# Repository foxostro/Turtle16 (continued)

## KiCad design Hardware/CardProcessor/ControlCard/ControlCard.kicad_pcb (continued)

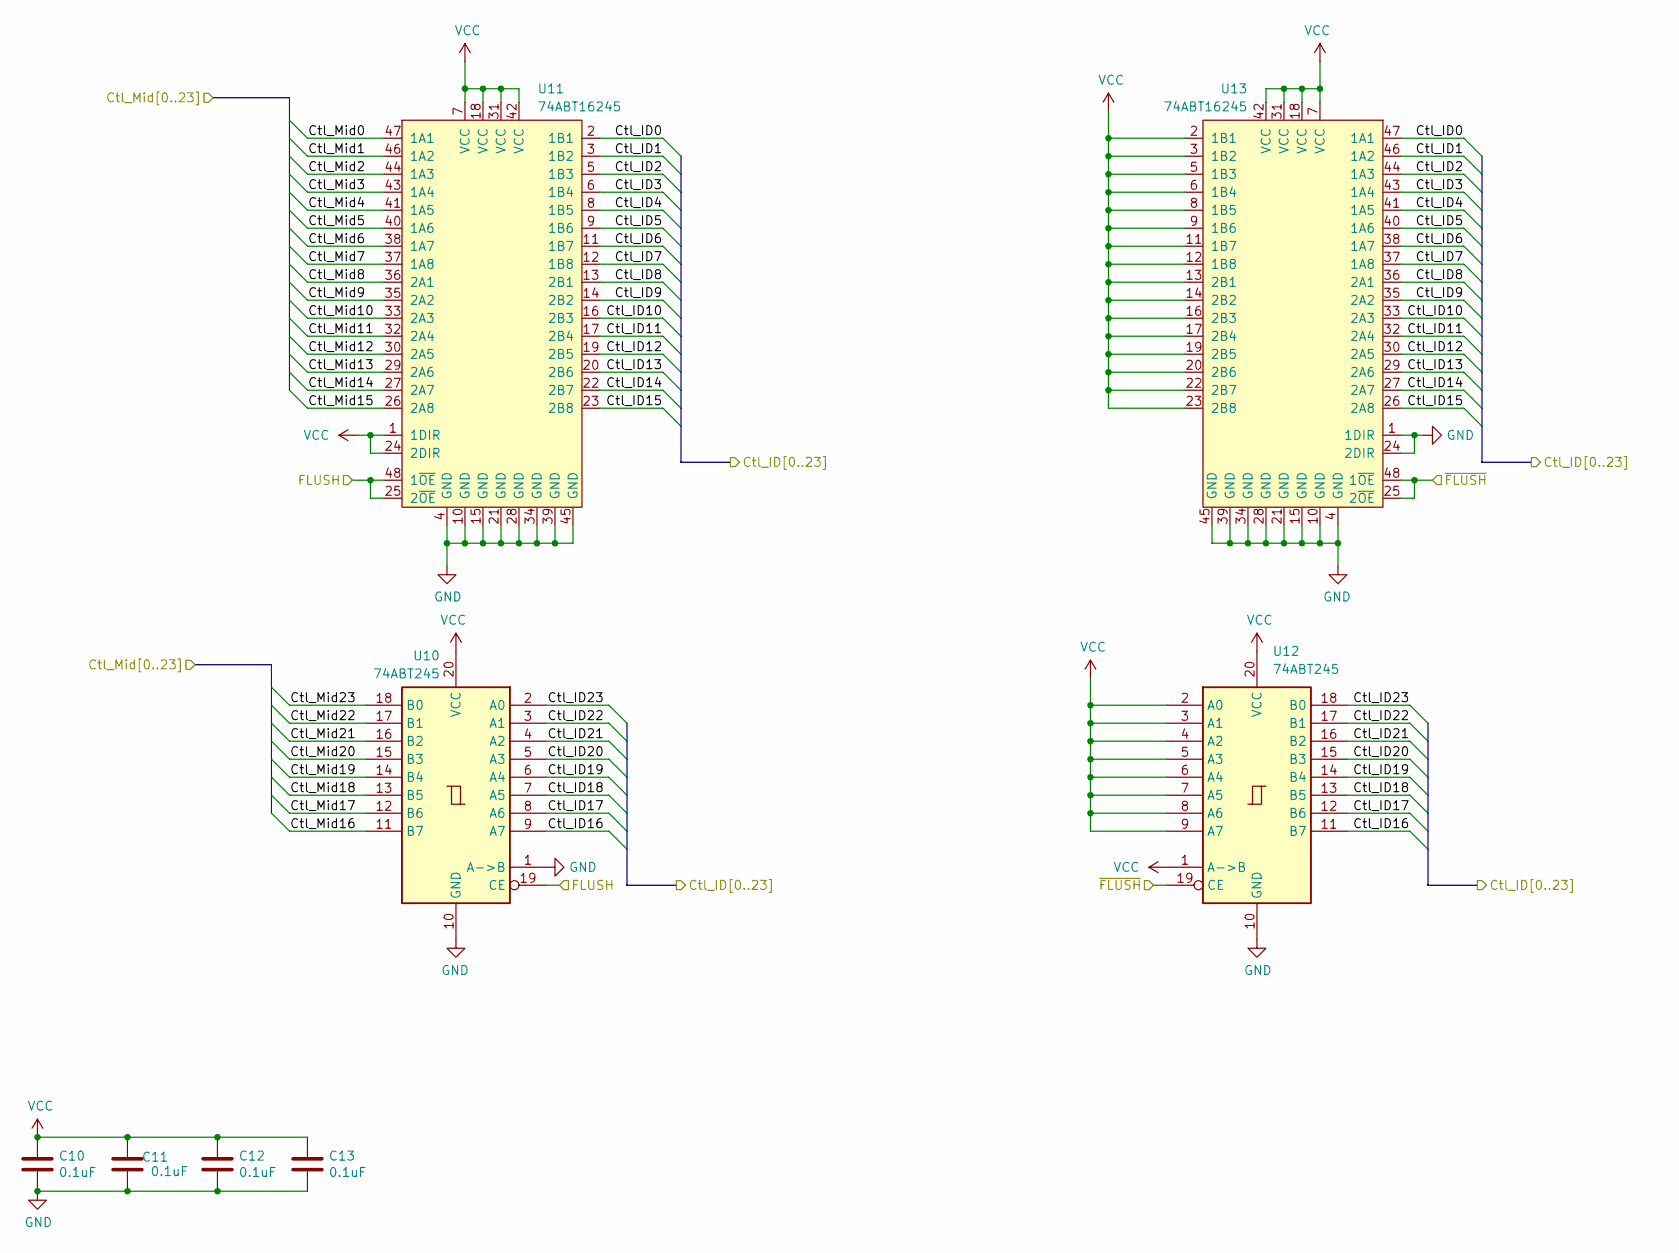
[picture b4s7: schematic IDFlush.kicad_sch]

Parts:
C10, C11, C12, C13: 0.1uF; C_0603_1608Metric; Manufacturer# EMK107B7104KAHT; Mouser# 963-EMK107B7104KAHT
U10, U12: 74ABT245; TSSOP-20_4.4x6.5mm_P0.65mm; Manufacturer# SN74ABT245BPWR; Mouser# 595-SN74ABT245BPWR
U11, U13: 74ABT16245; TSSOP-48_6.1x12.5mm_P0.5mm; Manufacturer# SN74ABTH16245DGGR; Mouser# 595-SNABTH16245DGGR

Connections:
/ID/Ctl_Mid0: U11.47 (1A1); also elsewhere on the board
/ID/Ctl_Mid1: U11.46 (1A2); also elsewhere on the board
/ID/Ctl_Mid2: U11.44 (1A3); also elsewhere on the board
/ID/Ctl_Mid3: U11.43 (1A4); also elsewhere on the board
/ID/Ctl_Mid4: U11.41 (1A5); also elsewhere on the board
/ID/Ctl_Mid5: U11.40 (1A6); also elsewhere on the board
/ID/Ctl_Mid6: U11.38 (1A7); also elsewhere on the board
/ID/Ctl_Mid7: U11.37 (1A8); also elsewhere on the board
/ID/Ctl_Mid8: U11.36 (2A1); also elsewhere on the board
/ID/Ctl_Mid9: U11.35 (2A2); also elsewhere on the board
/ID/Ctl_Mid10: U11.33 (2A3); also elsewhere on the board
/ID/Ctl_Mid11: U11.32 (2A4); also elsewhere on the board
/ID/Ctl_Mid12: U11.30 (2A5); also elsewhere on the board
/ID/Ctl_Mid13: U11.29 (2A6); also elsewhere on the board
/ID/Ctl_Mid14: U11.27 (2A7); also elsewhere on the board
/ID/Ctl_Mid15: U11.26 (2A8); also elsewhere on the board
/ID/Ctl_Mid16: U10.11 (B7); also elsewhere on the board
/ID/Ctl_Mid17: U10.12 (B6); also elsewhere on the board
/ID/Ctl_Mid18: U10.13 (B5); also elsewhere on the board
/ID/Ctl_Mid19: U10.14 (B4); also elsewhere on the board
/ID/Ctl_Mid20: U10.15 (B3); also elsewhere on the board
/ID/Ctl_Mid21: U10.16 (B2); also elsewhere on the board
/ID/Ctl_Mid22: U10.17 (B1); also elsewhere on the board
/ID/Ctl_Mid23: U10.18 (B0); also elsewhere on the board
/ID/Hazard Control/FLUSH: U10.19 (CE), U11.25 (2~OE), U11.48 (1~OE); also elsewhere on the board
/ID/Hazard Control/~FLUSH: U12.19 (CE), U13.25 (2~OE), U13.48 (1~OE); also elsewhere on the board
/ID/ID Flush/Ctl_ID0: U11.2 (1B1), U13.47 (1A1); also elsewhere on the board
/ID/ID Flush/Ctl_ID1: U11.3 (1B2), U13.46 (1A2); also elsewhere on the board
/ID/ID Flush/Ctl_ID2: U11.5 (1B3), U13.44 (1A3); also elsewhere on the board
/ID/ID Flush/Ctl_ID3: U11.6 (1B4), U13.43 (1A4); also elsewhere on the board
/ID/ID Flush/Ctl_ID4: U11.8 (1B5), U13.41 (1A5); also elsewhere on the board
/ID/ID Flush/Ctl_ID5: U11.9 (1B6), U13.40 (1A6); also elsewhere on the board
/ID/ID Flush/Ctl_ID6: U11.11 (1B7), U13.38 (1A7); also elsewhere on the board
/ID/ID Flush/Ctl_ID7: U11.12 (1B8), U13.37 (1A8); also elsewhere on the board
/ID/ID Flush/Ctl_ID8: U11.13 (2B1), U13.36 (2A1); also elsewhere on the board
/ID/ID Flush/Ctl_ID9: U11.14 (2B2), U13.35 (2A2); also elsewhere on the board
/ID/ID Flush/Ctl_ID10: U11.16 (2B3), U13.33 (2A3); also elsewhere on the board
/ID/ID Flush/Ctl_ID11: U11.17 (2B4), U13.32 (2A4); also elsewhere on the board
/ID/ID Flush/Ctl_ID12: U11.19 (2B5), U13.30 (2A5); also elsewhere on the board
/ID/ID Flush/Ctl_ID13: U11.20 (2B6), U13.29 (2A6); also elsewhere on the board
/ID/ID Flush/Ctl_ID14: U11.22 (2B7), U13.27 (2A7); also elsewhere on the board
/ID/ID Flush/Ctl_ID15: U11.23 (2B8), U13.26 (2A8); also elsewhere on the board
/ID/ID Flush/Ctl_ID16: U10.9 (A7), U12.11 (B7); also elsewhere on the board
/ID/ID Flush/Ctl_ID17: U10.8 (A6), U12.12 (B6); also elsewhere on the board
/ID/ID Flush/Ctl_ID18: U10.7 (A5), U12.13 (B5); also elsewhere on the board
/ID/ID Flush/Ctl_ID19: U10.6 (A4), U12.14 (B4); also elsewhere on the board
/ID/ID Flush/Ctl_ID20: U10.5 (A3), U12.15 (B3); also elsewhere on the board
/ID/ID Flush/Ctl_ID21: U10.4 (A2), U12.16 (B2); also elsewhere on the board
/ID/ID Flush/Ctl_ID22: U10.3 (A1), U12.17 (B1); also elsewhere on the board
/ID/ID Flush/Ctl_ID23: U10.2 (A0), U12.18 (B0); also elsewhere on the board
GND: C10.2, C11.2, C12.2, C13.2, U10.1 (A->B), U10.10 (GND), U11.4 (GND), U11.10 (GND), U11.15 (GND), U11.21 (GND), U11.28 (GND), U11.34 (GND), U11.39 (GND), U11.45 (GND), U12.10 (GND), U13.1 (1DIR), U13.4 (GND), U13.10 (GND), U13.15 (GND), U13.21 (GND), U13.24 (2DIR), U13.28 (GND), U13.34 (GND), U13.39 (GND), U13.45 (GND); also elsewhere on the board
VCC: C10.1, C11.1, C12.1, C13.1, U10.20 (VCC), U11.1 (1DIR), U11.7 (VCC), U11.18 (VCC), U11.24 (2DIR), U11.31 (VCC), U11.42 (VCC), U12.1 (A->B), U12.2 (A0), U12.3 (A1), U12.4 (A2), U12.5 (A3), U12.6 (A4), U12.7 (A5), U12.8 (A6), U12.9 (A7), U12.20 (VCC), U13.2 (1B1), U13.3 (1B2), U13.5 (1B3), U13.6 (1B4), U13.7 (VCC), U13.8 (1B5), U13.9 (1B6), U13.11 (1B7), U13.12 (1B8), U13.13 (2B1), U13.14 (2B2), U13.16 (2B3), U13.17 (2B4), U13.18 (VCC), U13.19 (2B5), U13.20 (2B6), U13.22 (2B7), U13.23 (2B8), U13.31 (VCC), U13.42 (VCC); also elsewhere on the board

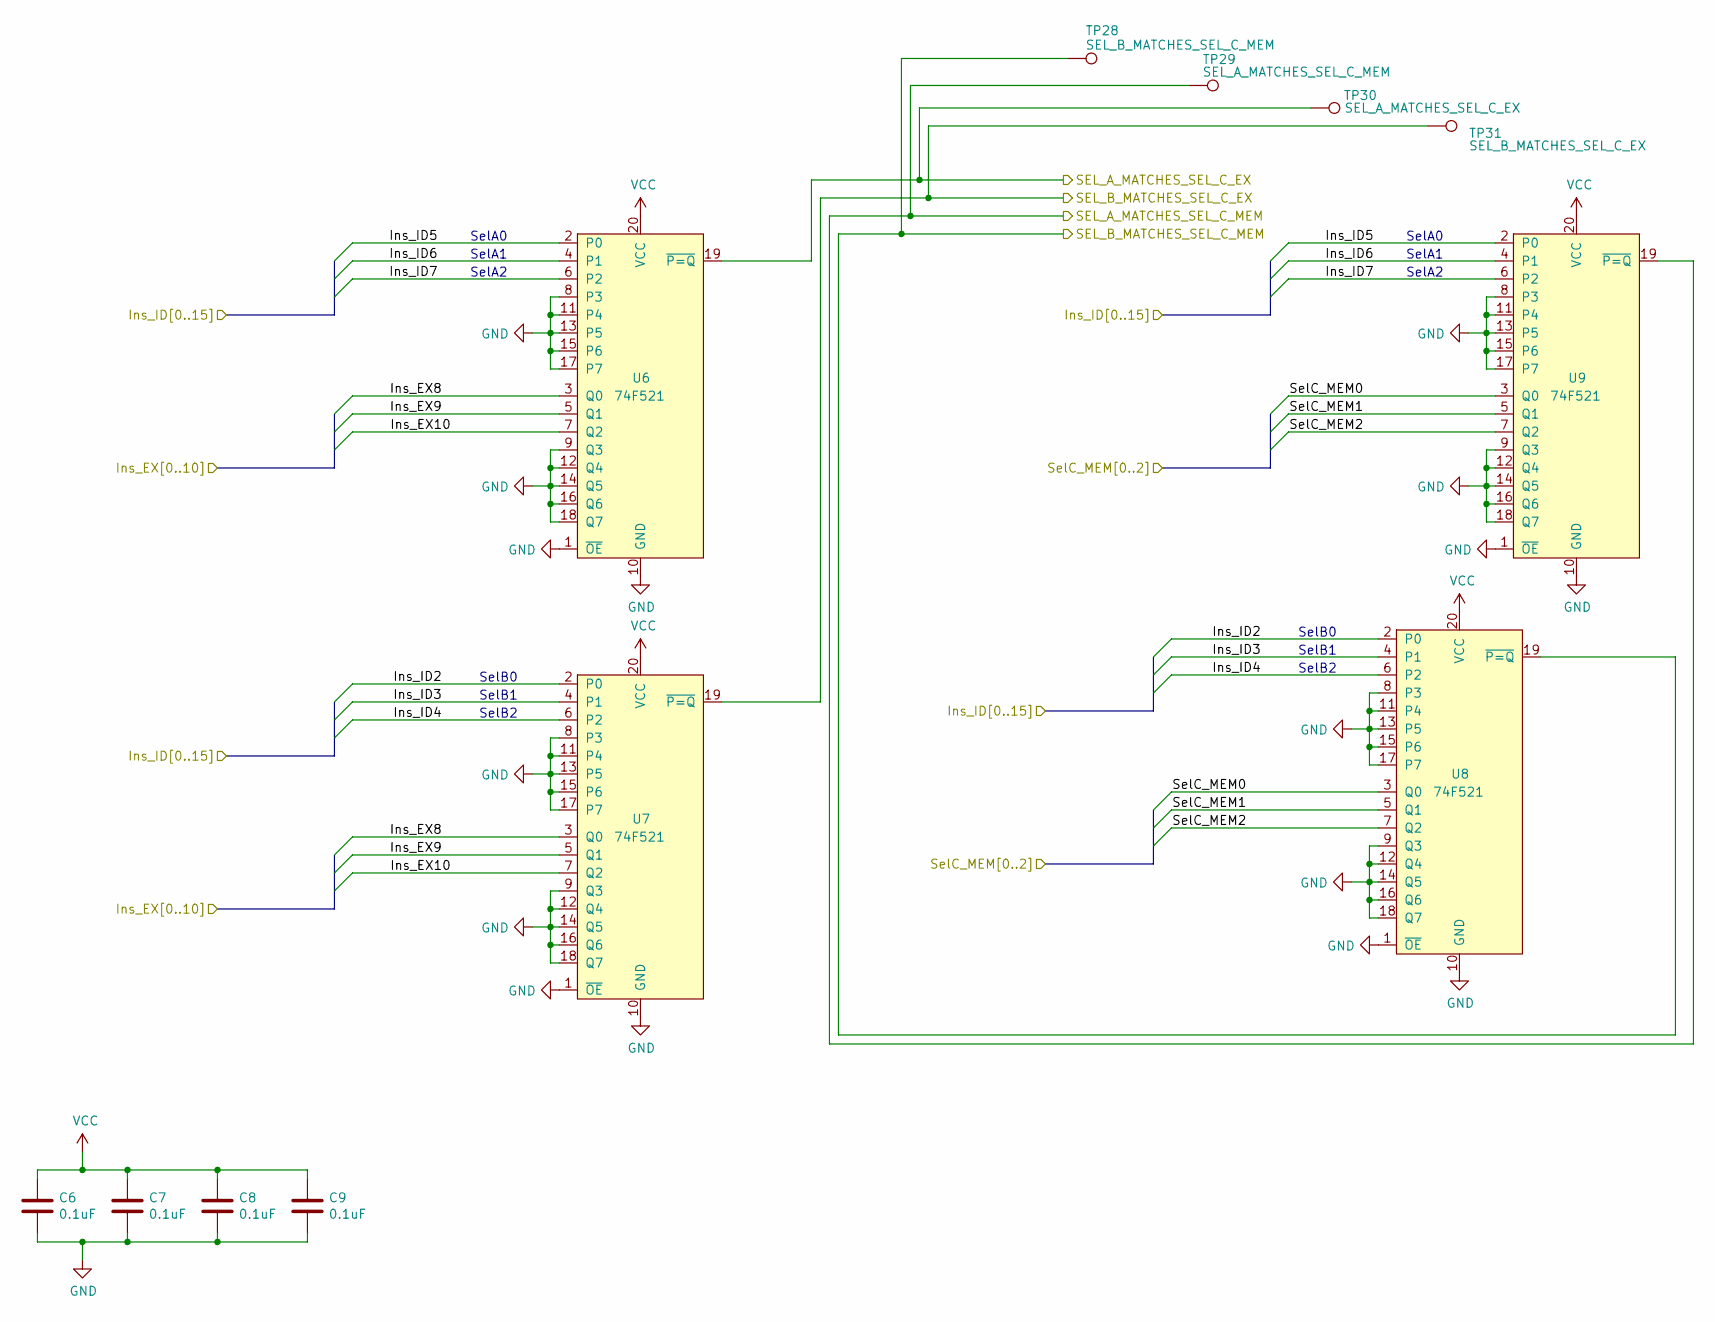
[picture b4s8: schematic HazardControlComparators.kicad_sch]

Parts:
C6, C7, C8, C9: 0.1uF; C_0603_1608Metric; Manufacturer# EMK107B7104KAHT; Mouser# 963-EMK107B7104KAHT
TP28: SEL_B_MATCHES_SEL_C_MEM; TestPoint_Pad_D1.0mm
TP29: SEL_A_MATCHES_SEL_C_MEM; TestPoint_Pad_D1.0mm
TP30: SEL_A_MATCHES_SEL_C_EX; TestPoint_Pad_D1.0mm
TP31: SEL_B_MATCHES_SEL_C_EX; TestPoint_Pad_D1.0mm
U6, U7, U8, U9: 74F521; SOIC-20W_7.5x12.8mm_P1.27mm; Manufacturer# SN74F521DWR; Mouser# 595-SN74F521DWR

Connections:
/CardEdgeControl/Ins_ID2: U7.2 (P0), U8.2 (P0); also elsewhere on the board
/CardEdgeControl/Ins_ID3: U7.4 (P1), U8.4 (P1); also elsewhere on the board
/CardEdgeControl/Ins_ID4: U7.6 (P2), U8.6 (P2); also elsewhere on the board
/CardEdgeControl/Ins_ID5: U6.2 (P0), U9.2 (P0); also elsewhere on the board
/CardEdgeControl/Ins_ID6: U6.4 (P1), U9.4 (P1); also elsewhere on the board
/CardEdgeControl/Ins_ID7: U6.6 (P2), U9.6 (P2); also elsewhere on the board
/CardEdgeControl/SelC_MEM0: U8.3 (Q0), U9.3 (Q0); also elsewhere on the board
/CardEdgeControl/SelC_MEM1: U8.5 (Q1), U9.5 (Q1); also elsewhere on the board
/CardEdgeControl/SelC_MEM2: U8.7 (Q2), U9.7 (Q2); also elsewhere on the board
/ID/Hazard Control/Hazard Control Comparators/SEL_A_MATCHES_SEL_C_EX: TP30.1, U6.19 (~P=Q); also elsewhere on the board
/ID/Hazard Control/Hazard Control Comparators/SEL_A_MATCHES_SEL_C_MEM: TP29.1, U9.19 (~P=Q); also elsewhere on the board
/ID/Hazard Control/Hazard Control Comparators/SEL_B_MATCHES_SEL_C_EX: TP31.1, U7.19 (~P=Q); also elsewhere on the board
/ID/Hazard Control/Hazard Control Comparators/SEL_B_MATCHES_SEL_C_MEM: TP28.1, U8.19 (~P=Q); also elsewhere on the board
/ID/Ins_EX8: U6.3 (Q0), U7.3 (Q0); also elsewhere on the board
/ID/Ins_EX9: U6.5 (Q1), U7.5 (Q1); also elsewhere on the board
/ID/Ins_EX10: U6.7 (Q2), U7.7 (Q2); also elsewhere on the board
GND: C6.2, C7.2, C8.2, C9.2, U6.1 (~OE), U6.8 (P3), U6.9 (Q3), U6.10 (GND), U6.11 (P4), U6.12 (Q4), U6.13 (P5), U6.14 (Q5), U6.15 (P6), U6.16 (Q6), U6.17 (P7), U6.18 (Q7), U7.1 (~OE), U7.8 (P3), U7.9 (Q3), U7.10 (GND), U7.11 (P4), U7.12 (Q4), U7.13 (P5), U7.14 (Q5), U7.15 (P6), U7.16 (Q6), U7.17 (P7), U7.18 (Q7), U8.1 (~OE), U8.8 (P3), U8.9 (Q3), U8.10 (GND), U8.11 (P4), U8.12 (Q4), U8.13 (P5), U8.14 (Q5), U8.15 (P6), U8.16 (Q6), U8.17 (P7), U8.18 (Q7), U9.1 (~OE), U9.8 (P3), U9.9 (Q3), U9.10 (GND), U9.11 (P4), U9.12 (Q4), U9.13 (P5), U9.14 (Q5), U9.15 (P6), U9.16 (Q6), U9.17 (P7), U9.18 (Q7); also elsewhere on the board
VCC: C6.1, C7.1, C8.1, C9.1, U6.20 (VCC), U7.20 (VCC), U8.20 (VCC), U9.20 (VCC); also elsewhere on the board

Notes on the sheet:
SelA0
SelB1
SelA2
SelA1
SelB2
SelB0

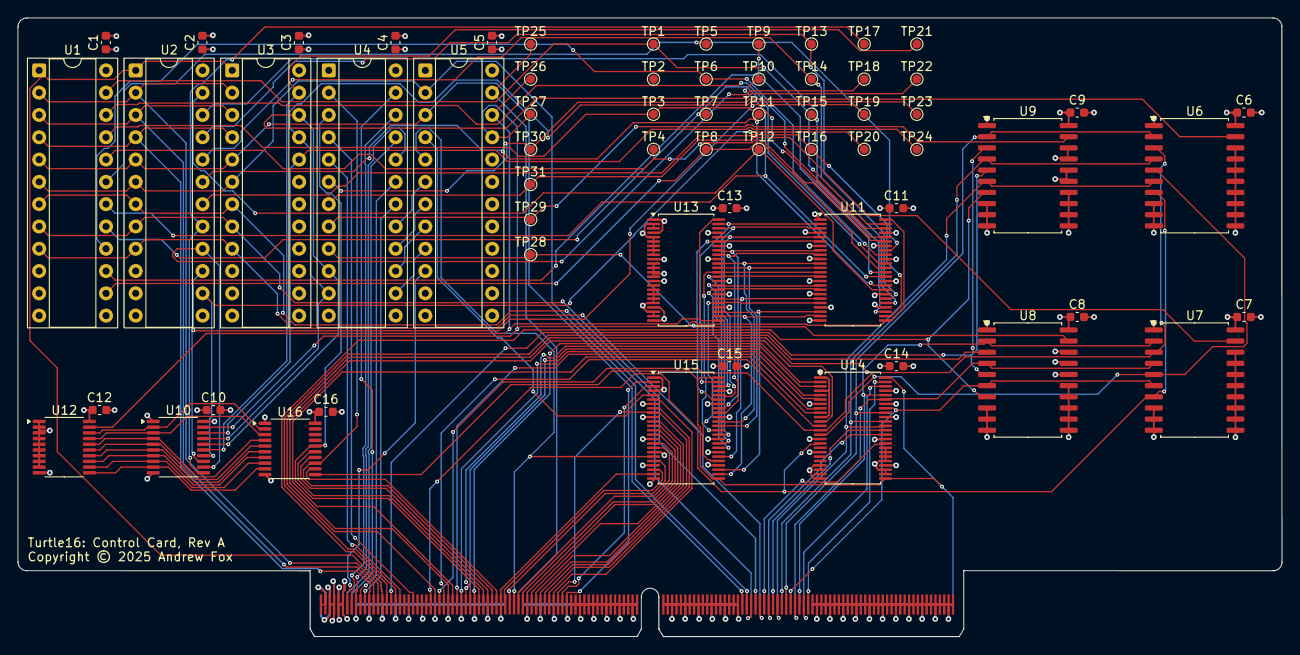
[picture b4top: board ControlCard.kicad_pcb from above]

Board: 4 copper layers, 144.0 x 70.5 mm, 64 parts (0 on the bottom side), 126 nets.

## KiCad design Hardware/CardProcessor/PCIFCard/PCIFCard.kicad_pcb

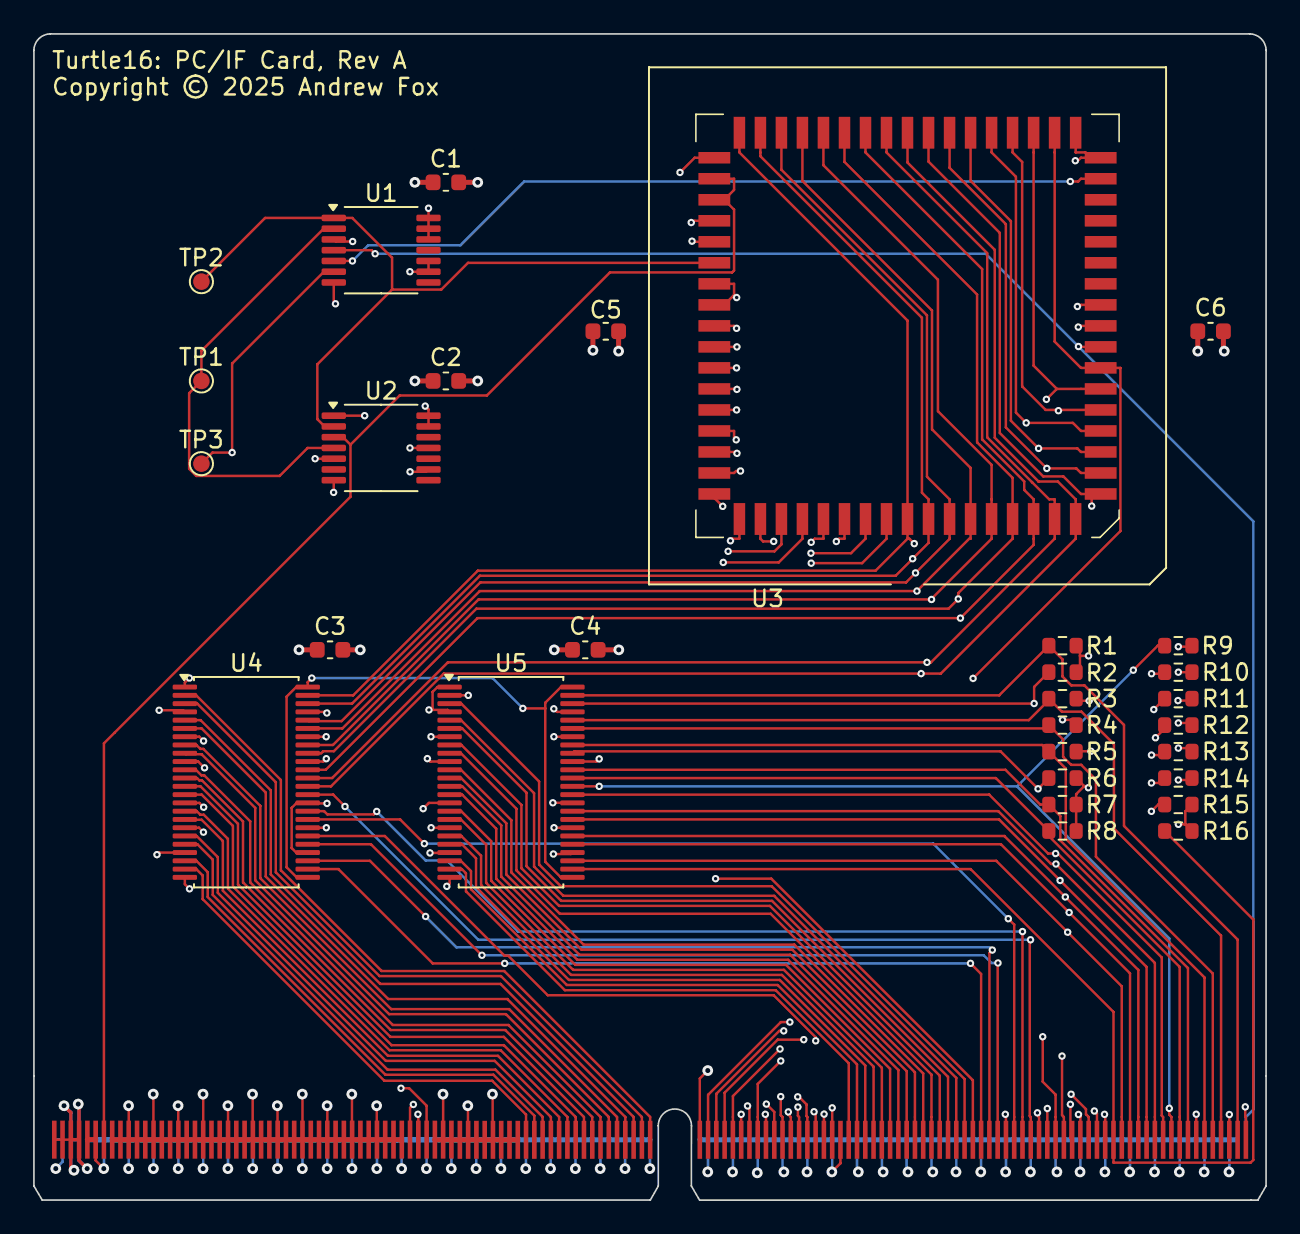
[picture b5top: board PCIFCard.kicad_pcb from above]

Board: 6 copper layers, 74.5 x 70.5 mm, 31 parts (0 on the bottom side), 91 nets.

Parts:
C1, C2, C3, C4, C5, C6: 0.1uF; C_0603_1608Metric
J1: MEC5-140-01-L-DV-W1-K; MEC5-140-01-L-DV-W1-K_Edge
R1, R2, R3, R4, R5, R6, R7, R8, R9, R10, R11, R12, R13, R14, R15, R16: 10K; R_0603_1608Metric
TP1: TP; TestPoint_Pad_D1.0mm
TP2: RS1; TestPoint_Pad_D1.0mm
TP3: CLK; TestPoint_Pad_D1.0mm
U1: 74ABT32; TSSOP-14_4.4x5mm_P0.65mm
U2: 74AHCT04; TSSOP-14_4.4x5mm_P0.65mm
U3: IDT7381; PLCC-68_SMD-Socket
U4, U5: 74ABT16374; TSSOP-48_6.1x12.5mm_P0.5mm

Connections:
/CardEdgePCIF/FLUSH_IF: J1.279, U1.3
/CardEdgePCIF/Ins_ID0: J1.213, U5.2 (1Q1)
/CardEdgePCIF/Ins_ID1: J1.211, U5.3 (1Q2)
/CardEdgePCIF/Ins_ID2: J1.209, U5.5 (1Q3)
/CardEdgePCIF/Ins_ID3: J1.207, U5.6 (1Q4)
/CardEdgePCIF/Ins_ID4: J1.205, U5.8 (1Q5)
/CardEdgePCIF/Ins_ID5: J1.203, U5.9 (1Q6)
/CardEdgePCIF/Ins_ID6: J1.201, U5.11 (1Q7)
/CardEdgePCIF/Ins_ID7: J1.199, U5.12 (1Q8)
/CardEdgePCIF/Ins_ID8: J1.197, U5.13 (2Q1)
/CardEdgePCIF/Ins_ID9: J1.195, U5.14 (2Q2)
/CardEdgePCIF/Ins_ID10: J1.193, U5.16 (2Q3)
/CardEdgePCIF/Ins_ID11: J1.191, U5.17 (2Q4)
/CardEdgePCIF/Ins_ID12: J1.189, U5.19 (2Q5)
/CardEdgePCIF/Ins_ID13: J1.187, U5.20 (2Q6)
/CardEdgePCIF/Ins_ID14: J1.185, U5.22 (2Q7)
/CardEdgePCIF/Ins_ID15: J1.183, U5.23 (2Q8)
/CardEdgePCIF/Ins_IF0: J1.277, R1.1, U5.47 (1D1)
/CardEdgePCIF/Ins_IF1: J1.275, R2.1, U5.46 (1D2)
/CardEdgePCIF/Ins_IF2: J1.273, R3.1, U5.44 (1D3)
/CardEdgePCIF/Ins_IF3: J1.271, R4.1, U5.43 (1D4)
/CardEdgePCIF/Ins_IF4: J1.269, R5.1, U5.41 (1D5)
/CardEdgePCIF/Ins_IF5: J1.267, R6.1, U5.40 (1D6)
/CardEdgePCIF/Ins_IF6: J1.265, R7.1, U5.38 (1D7)
/CardEdgePCIF/Ins_IF7: J1.263, R8.1, U5.37 (1D8)
/CardEdgePCIF/Ins_IF8: J1.261, R9.1, U5.36 (2D1)
/CardEdgePCIF/Ins_IF9: J1.259, R10.1, U5.35 (2D2)
/CardEdgePCIF/Ins_IF10: J1.257, R11.1, U5.33 (2D3)
/CardEdgePCIF/Ins_IF11: J1.255, R12.1, U5.32 (2D4)
/CardEdgePCIF/Ins_IF12: J1.253, R13.1, U5.30 (2D5)
/CardEdgePCIF/Ins_IF13: J1.251, R14.1, U5.29 (2D6)
/CardEdgePCIF/Ins_IF14: J1.249, R15.1, U5.27 (2D7)
/CardEdgePCIF/Ins_IF15: J1.247, R16.1, U5.26 (2D8)
/CardEdgePCIF/PC_EX0: J1.145, U4.2 (1Q1)
/CardEdgePCIF/PC_EX1: J1.143, U4.3 (1Q2)
/CardEdgePCIF/PC_EX2: J1.141, U4.5 (1Q3)
/CardEdgePCIF/PC_EX3: J1.139, U4.6 (1Q4)
/CardEdgePCIF/PC_EX4: J1.137, U4.8 (1Q5)
/CardEdgePCIF/PC_EX5: J1.135, U4.9 (1Q6)
/CardEdgePCIF/PC_EX6: J1.133, U4.11 (1Q7)
/CardEdgePCIF/PC_EX7: J1.131, U4.12 (1Q8)
/CardEdgePCIF/PC_EX8: J1.129, U4.13 (2Q1)
/CardEdgePCIF/PC_EX9: J1.127, U4.14 (2Q2)
/CardEdgePCIF/PC_EX10: J1.125, U4.16 (2Q3)
/CardEdgePCIF/PC_EX11: J1.123, U4.17 (2Q4)
/CardEdgePCIF/PC_EX12: J1.121, U4.19 (2Q5)
/CardEdgePCIF/PC_EX13: J1.119, U4.20 (2Q6)
/CardEdgePCIF/PC_EX14: J1.117, U4.22 (2Q7)
/CardEdgePCIF/PC_EX15: J1.115, U4.23 (2Q8)
/CardEdgePCIF/Phi1a: J1.280, U1.4, U3.17 (CLK)
/CardEdgePCIF/STALL: J1.91, U1.5, U3.25 (~ENF)
/CardEdgePCIF/Y_EX0: J1.179, U3.53 (B0)
/CardEdgePCIF/Y_EX1: J1.177, U3.54 (B1)
/CardEdgePCIF/Y_EX2: J1.175, U3.55 (B2)
/CardEdgePCIF/Y_EX3: J1.173, U3.56 (B3)
/CardEdgePCIF/Y_EX4: J1.171, U3.57 (B4)
/CardEdgePCIF/Y_EX5: J1.169, U3.58 (B5)
/CardEdgePCIF/Y_EX6: J1.167, U3.59 (B6)
/CardEdgePCIF/Y_EX7: J1.165, U3.60 (B7)
/CardEdgePCIF/Y_EX8: J1.163, U3.61 (B8)
/CardEdgePCIF/Y_EX9: J1.161, U3.62 (B9)
/CardEdgePCIF/Y_EX10: J1.159, U3.63 (B10)
/CardEdgePCIF/Y_EX11: J1.157, U3.64 (B11)
/CardEdgePCIF/Y_EX12: J1.155, U3.65 (B12)
/CardEdgePCIF/Y_EX13: J1.153, U3.66 (B13)
/CardEdgePCIF/Y_EX14: J1.151, U3.67 (B14)
/CardEdgePCIF/Y_EX15: J1.149, U3.68 (B15)
/CardEdgePCIF/~JABS: J1.87, U3.48 (RS0)
/CardEdgePCIF/~J: J1.89, U2.1, U3.44 (C0)
/CardEdgePCIF/~RST_sync: J1.13, U2.3, U3.45 (I0), U3.46 (I1)
/IF/sheet5FE3DA15/PC0: J1.245, U3.1 (A0), U3.43 (F0), U4.47 (1D1)
/IF/sheet5FE3DA15/PC1: J1.243, U3.2 (A1), U3.42 (F1), U4.46 (1D2)
/IF/sheet5FE3DA15/PC2: J1.241, U3.3 (A2), U3.41 (F2), U4.44 (1D3)
/IF/sheet5FE3DA15/PC3: J1.239, U3.4 (A3), U3.40 (F3), U4.43 (1D4)
/IF/sheet5FE3DA15/PC4: J1.237, U3.5 (A4), U3.39 (F4), U4.41 (1D5)
/IF/sheet5FE3DA15/PC5: J1.235, U3.6 (A5), U3.38 (F5), U4.40 (1D6)
/IF/sheet5FE3DA15/PC6: J1.233, U3.7 (A6), U3.37 (F6), U4.38 (1D7)
/IF/sheet5FE3DA15/PC7: J1.231, U3.8 (A7), U3.36 (F7), U4.37 (1D8)
/IF/sheet5FE3DA15/PC8: J1.229, U3.9 (A8), U3.35 (F8), U4.36 (2D1)
/IF/sheet5FE3DA15/PC9: J1.227, U3.10 (A9), U3.34 (F9), U4.35 (2D2)
/IF/sheet5FE3DA15/PC10: J1.225, U3.11 (A10), U3.33 (F10), U4.33 (2D3)
/IF/sheet5FE3DA15/PC11: J1.223, U3.12 (A11), U3.32 (F11), U4.32 (2D4)
/IF/sheet5FE3DA15/PC12: J1.221, U3.13 (A12), U3.31 (F12), U4.30 (2D5)
/IF/sheet5FE3DA15/PC13: J1.219, U3.14 (A13), U3.30 (F13), U4.29 (2D6)
/IF/sheet5FE3DA15/PC14: J1.217, U3.15 (A14), U3.29 (F14), U4.27 (2D7)
/IF/sheet5FE3DA15/PC15: J1.215, U3.16 (A15), U3.28 (F15), U4.26 (2D8)
GND: C1.2, C2.2, C3.2, C4.2, C5.2, C6.2, J1.2, J1.4, J1.9, J1.10, J1.11, J1.12, J1.14, J1.15, J1.16, J1.17, J1.18, J1.19, J1.20, J1.21, J1.22, J1.23, J1.24, J1.25, J1.26, J1.27, J1.28, J1.29, J1.30, J1.31, J1.32, J1.33, J1.34, J1.35, J1.36, J1.37, J1.38, J1.39, J1.40, J1.41, J1.42, J1.43, J1.44, J1.45, J1.46, J1.47, J1.48, J1.49, J1.50, J1.51, J1.52, J1.53, J1.54, J1.55, J1.56, J1.57, J1.58, J1.59, J1.60, J1.61, J1.62, J1.63, J1.64, J1.65, J1.66, J1.67, J1.68, J1.69, J1.70, J1.71, J1.72, J1.73, J1.74, J1.75, J1.76, J1.77, J1.78, J1.79, J1.80, J1.81, J1.82, J1.83, J1.84, J1.85, J1.86, J1.88, J1.90, J1.92, J1.93, J1.94, J1.95, J1.96, J1.97, J1.98, J1.99, J1.100, J1.101, J1.102, J1.103, J1.104, J1.105, J1.106, J1.107, J1.108, J1.109, J1.110, J1.111, J1.112, J1.113, J1.114, J1.116, J1.118, J1.120, J1.122, J1.124, J1.126, J1.128, J1.130, J1.132, J1.134, J1.136, J1.138, J1.140, J1.142, J1.144, J1.146, J1.147, J1.148, J1.150, J1.152, J1.154, J1.156, J1.158, J1.160, J1.162, J1.164, J1.166, J1.168, J1.170, J1.172, J1.174, J1.176, J1.178, J1.180, J1.181, J1.182, J1.184, J1.186, J1.188, J1.190, J1.192, J1.194, J1.196, J1.198, J1.200, J1.202, J1.204, J1.206, J1.208, J1.210, J1.212, J1.214, J1.216, J1.218, J1.220, J1.222, J1.224, J1.226, J1.228, J1.230, J1.232, J1.234, J1.236, J1.238, J1.240, J1.242, J1.244, J1.246, J1.248, J1.250, J1.252, J1.254, J1.256, J1.258, J1.260, J1.262, J1.264, J1.266, J1.268, J1.270, J1.272, J1.274, J1.276, J1.278, R1.2, R2.2, R3.2, R4.2, R5.2, R6.2, R7.2, R8.2, R9.2, R10.2, R11.2, R12.2, R13.2, R14.2, R15.2, R16.2, U1.7 (GND), U2.7 (GND), U3.19 (GND), U3.26 (FTF), U3.27 (~OE), U3.47 (I2), U4.1 (1~OE), U4.4 (GND), U4.10 (GND), U4.15 (GND), U4.21 (GND), U4.24 (2~OE), U4.28 (GND), U4.34 (GND), U4.39 (GND), U4.45 (GND), U5.1 (1~OE), U5.4 (GND), U5.10 (GND), U5.15 (GND), U5.21 (GND), U5.24 (2~OE), U5.28 (GND), U5.34 (GND), U5.39 (GND), U5.45 (GND)
unnamed: TP1.1, U1.2, U2.4
unnamed: TP2.1, U1.1, U2.2, U3.49 (RS1)
unnamed: TP3.1, U1.6, U4.25 (2CLK), U4.48 (1CLK), U5.25 (2CLK), U5.48 (1CLK)
VCC: C1.1, C2.1, C3.1, C4.1, C5.1, C6.1, J1.1, J1.3, J1.5, J1.6, J1.7, J1.8, U1.9, U1.10, U1.12, U1.13, U1.14 (VCC), U2.5, U2.9, U2.11, U2.13, U2.14 (VCC), U3.18 (VCC), U3.50 (FTAB), U3.51 (~ENB), U3.52 (~ENA), U4.7 (VCC), U4.18 (VCC), U4.31 (VCC), U4.42 (VCC), U5.7 (VCC), U5.18 (VCC), U5.31 (VCC), U5.42 (VCC)

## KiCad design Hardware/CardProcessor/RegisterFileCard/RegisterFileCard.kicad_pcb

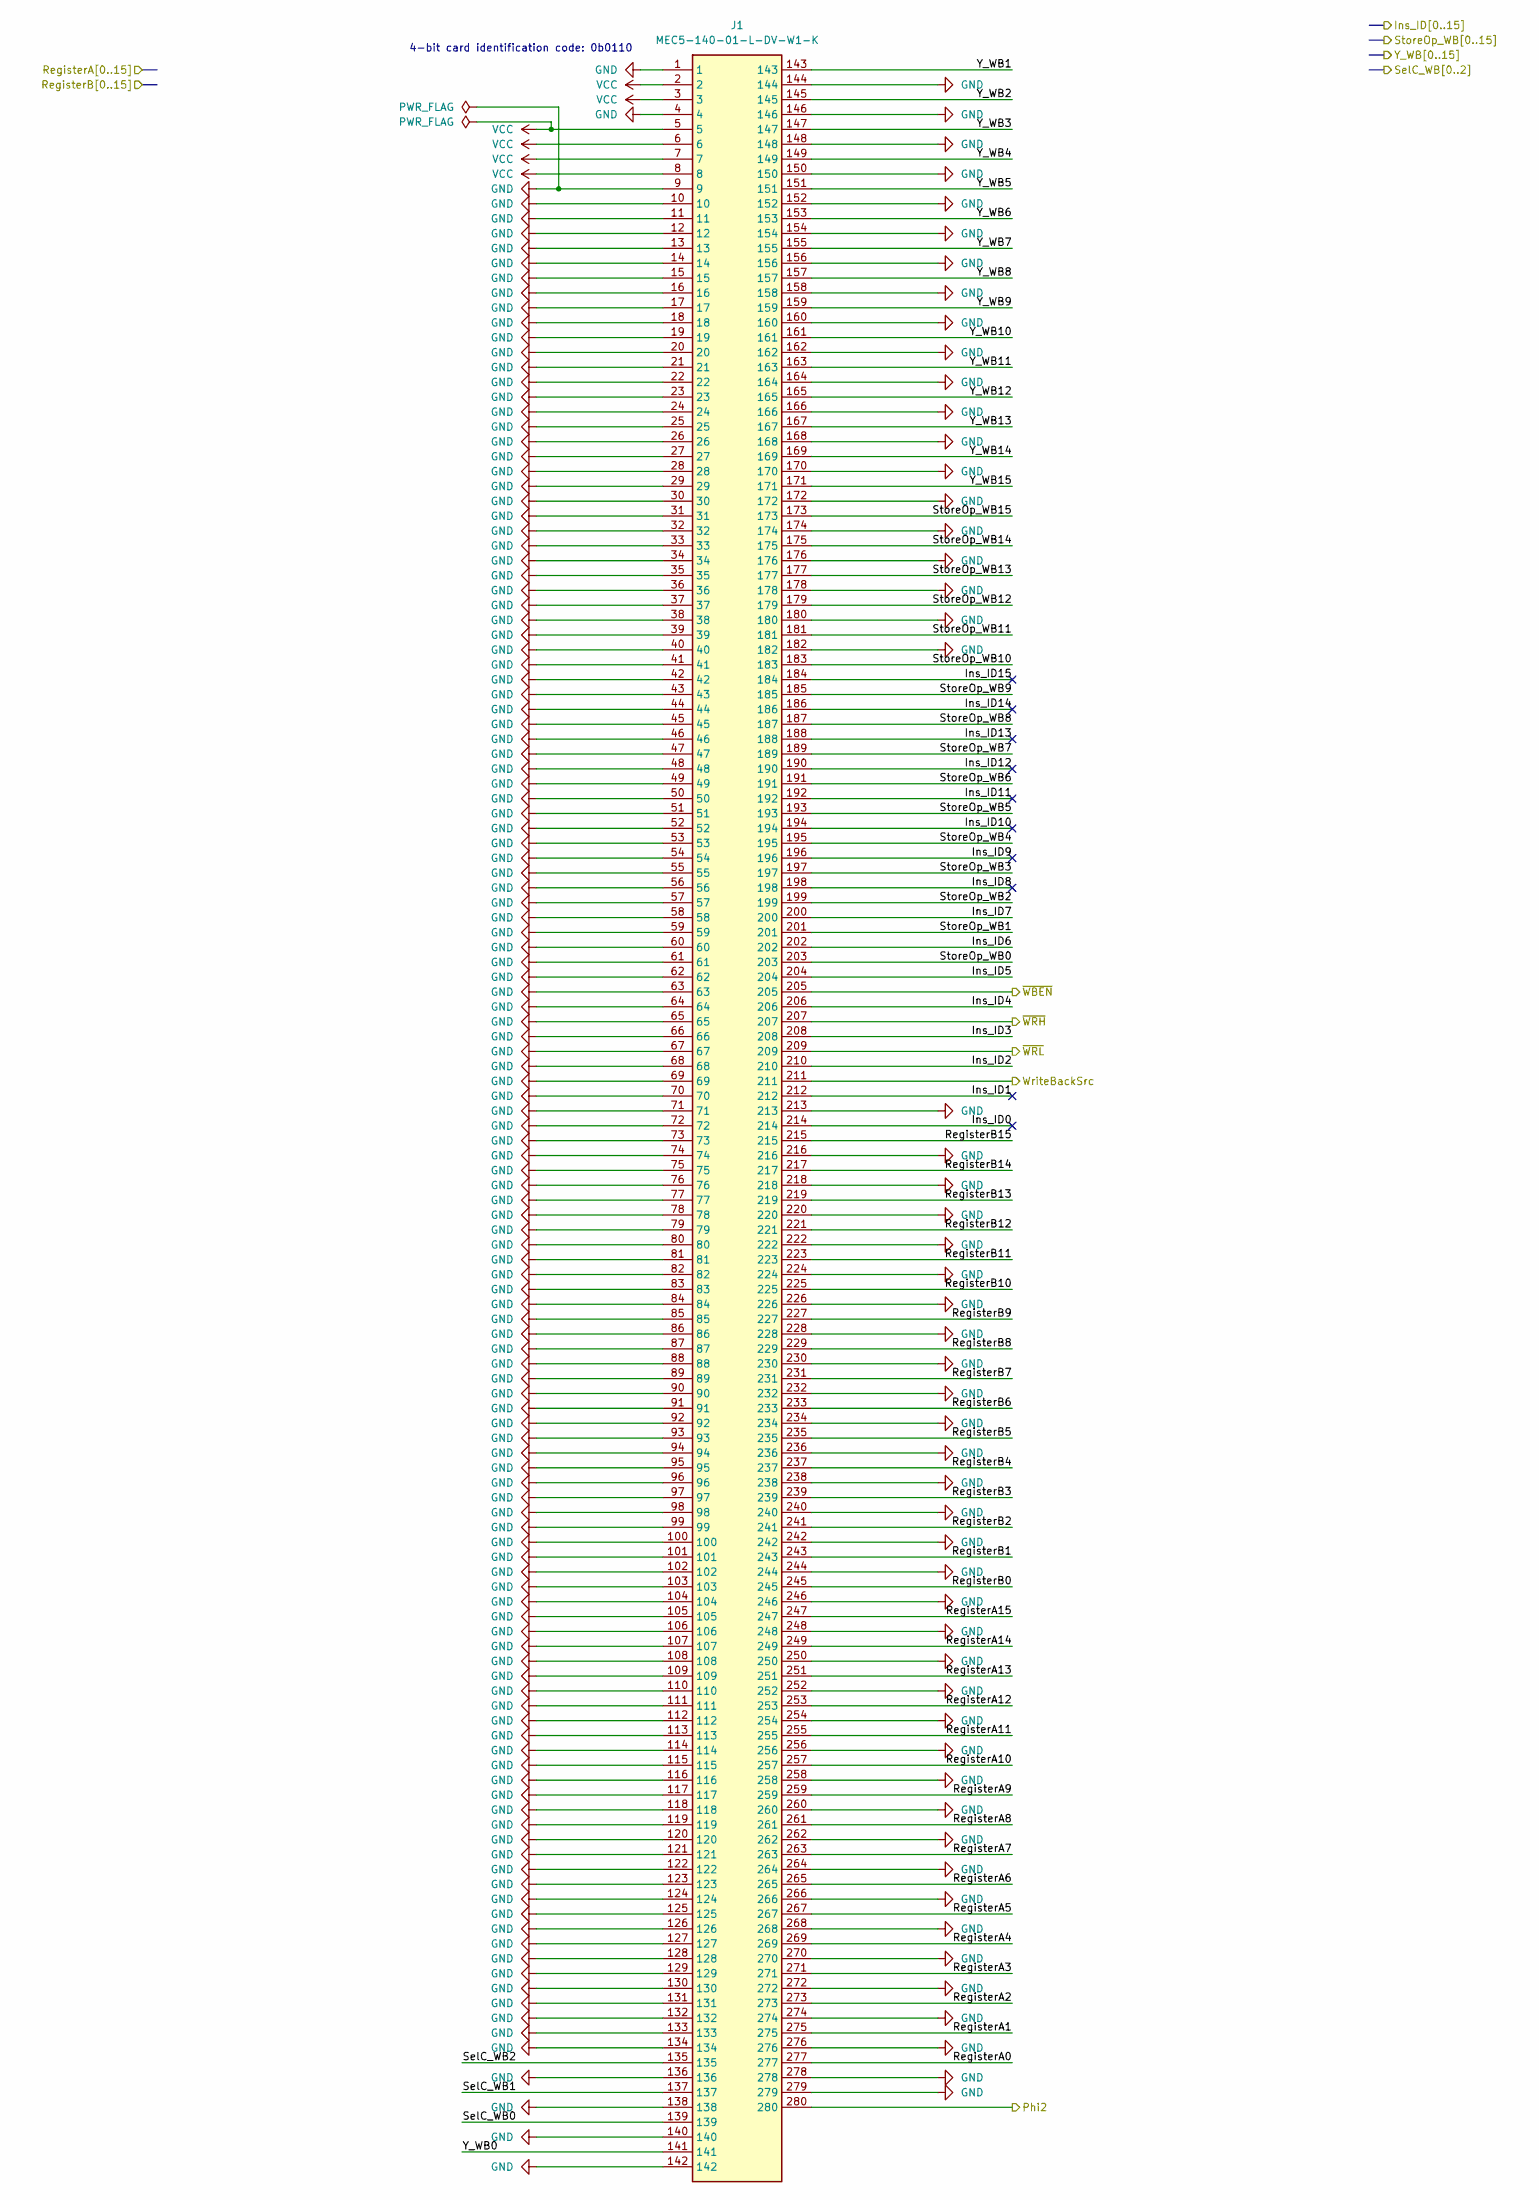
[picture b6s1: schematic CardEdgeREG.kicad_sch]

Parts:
J1: MEC5-140-01-L-DV-W1-K; MEC5-140-01-L-DV-W1-K_Edge; Mouser Part Number 200-MEC514001LDVW1K

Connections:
/CardEdgeREG/Ins_ID0: J1.214
/CardEdgeREG/Ins_ID1: J1.212
/CardEdgeREG/Ins_ID2: J1.210; also elsewhere on the board
/CardEdgeREG/Ins_ID3: J1.208; also elsewhere on the board
/CardEdgeREG/Ins_ID4: J1.206; also elsewhere on the board
/CardEdgeREG/Ins_ID5: J1.204; also elsewhere on the board
/CardEdgeREG/Ins_ID6: J1.202; also elsewhere on the board
/CardEdgeREG/Ins_ID7: J1.200; also elsewhere on the board
/CardEdgeREG/Ins_ID8: J1.198
/CardEdgeREG/Ins_ID9: J1.196
/CardEdgeREG/Ins_ID10: J1.194
/CardEdgeREG/Ins_ID11: J1.192
/CardEdgeREG/Ins_ID12: J1.190
/CardEdgeREG/Ins_ID13: J1.188
/CardEdgeREG/Ins_ID14: J1.186
/CardEdgeREG/Ins_ID15: J1.184
/CardEdgeREG/Phi2: J1.280; also elsewhere on the board
/CardEdgeREG/RegisterA0: J1.277; also elsewhere on the board
/CardEdgeREG/RegisterA1: J1.275; also elsewhere on the board
/CardEdgeREG/RegisterA2: J1.273; also elsewhere on the board
/CardEdgeREG/RegisterA3: J1.271; also elsewhere on the board
/CardEdgeREG/RegisterA4: J1.269; also elsewhere on the board
/CardEdgeREG/RegisterA5: J1.267; also elsewhere on the board
/CardEdgeREG/RegisterA6: J1.265; also elsewhere on the board
/CardEdgeREG/RegisterA7: J1.263; also elsewhere on the board
/CardEdgeREG/RegisterA8: J1.261; also elsewhere on the board
/CardEdgeREG/RegisterA9: J1.259; also elsewhere on the board
/CardEdgeREG/RegisterA10: J1.257; also elsewhere on the board
/CardEdgeREG/RegisterA11: J1.255; also elsewhere on the board
/CardEdgeREG/RegisterA12: J1.253; also elsewhere on the board
/CardEdgeREG/RegisterA13: J1.251; also elsewhere on the board
/CardEdgeREG/RegisterA14: J1.249; also elsewhere on the board
/CardEdgeREG/RegisterA15: J1.247; also elsewhere on the board
/CardEdgeREG/RegisterB0: J1.245; also elsewhere on the board
/CardEdgeREG/RegisterB1: J1.243; also elsewhere on the board
/CardEdgeREG/RegisterB2: J1.241; also elsewhere on the board
/CardEdgeREG/RegisterB3: J1.239; also elsewhere on the board
/CardEdgeREG/RegisterB4: J1.237; also elsewhere on the board
/CardEdgeREG/RegisterB5: J1.235; also elsewhere on the board
/CardEdgeREG/RegisterB6: J1.233; also elsewhere on the board
/CardEdgeREG/RegisterB7: J1.231; also elsewhere on the board
/CardEdgeREG/RegisterB8: J1.229; also elsewhere on the board
/CardEdgeREG/RegisterB9: J1.227; also elsewhere on the board
/CardEdgeREG/RegisterB10: J1.225; also elsewhere on the board
/CardEdgeREG/RegisterB11: J1.223; also elsewhere on the board
/CardEdgeREG/RegisterB12: J1.221; also elsewhere on the board
/CardEdgeREG/RegisterB13: J1.219; also elsewhere on the board
/CardEdgeREG/RegisterB14: J1.217; also elsewhere on the board
/CardEdgeREG/RegisterB15: J1.215; also elsewhere on the board
/CardEdgeREG/SelC_WB0: J1.139; also elsewhere on the board
/CardEdgeREG/SelC_WB1: J1.137; also elsewhere on the board
/CardEdgeREG/SelC_WB2: J1.135; also elsewhere on the board
/CardEdgeREG/StoreOp_WB0: J1.203; also elsewhere on the board
/CardEdgeREG/StoreOp_WB1: J1.201; also elsewhere on the board
/CardEdgeREG/StoreOp_WB2: J1.199; also elsewhere on the board
/CardEdgeREG/StoreOp_WB3: J1.197; also elsewhere on the board
/CardEdgeREG/StoreOp_WB4: J1.195; also elsewhere on the board
/CardEdgeREG/StoreOp_WB5: J1.193; also elsewhere on the board
/CardEdgeREG/StoreOp_WB6: J1.191; also elsewhere on the board
/CardEdgeREG/StoreOp_WB7: J1.189; also elsewhere on the board
/CardEdgeREG/StoreOp_WB8: J1.187; also elsewhere on the board
/CardEdgeREG/StoreOp_WB9: J1.185; also elsewhere on the board
/CardEdgeREG/StoreOp_WB10: J1.183; also elsewhere on the board
/CardEdgeREG/StoreOp_WB11: J1.181; also elsewhere on the board
/CardEdgeREG/StoreOp_WB12: J1.179; also elsewhere on the board
/CardEdgeREG/StoreOp_WB13: J1.177; also elsewhere on the board
/CardEdgeREG/StoreOp_WB14: J1.175; also elsewhere on the board
/CardEdgeREG/StoreOp_WB15: J1.173; also elsewhere on the board
/CardEdgeREG/WriteBackSrc: J1.211; also elsewhere on the board
/CardEdgeREG/Y_WB0: J1.141; also elsewhere on the board
/CardEdgeREG/Y_WB1: J1.143; also elsewhere on the board
/CardEdgeREG/Y_WB2: J1.145; also elsewhere on the board
/CardEdgeREG/Y_WB3: J1.147; also elsewhere on the board
/CardEdgeREG/Y_WB4: J1.149; also elsewhere on the board
/CardEdgeREG/Y_WB5: J1.151; also elsewhere on the board
/CardEdgeREG/Y_WB6: J1.153; also elsewhere on the board
/CardEdgeREG/Y_WB7: J1.155; also elsewhere on the board
/CardEdgeREG/Y_WB8: J1.157; also elsewhere on the board
/CardEdgeREG/Y_WB9: J1.159; also elsewhere on the board
/CardEdgeREG/Y_WB10: J1.161; also elsewhere on the board
/CardEdgeREG/Y_WB11: J1.163; also elsewhere on the board
/CardEdgeREG/Y_WB12: J1.165; also elsewhere on the board
/CardEdgeREG/Y_WB13: J1.167; also elsewhere on the board
/CardEdgeREG/Y_WB14: J1.169; also elsewhere on the board
/CardEdgeREG/Y_WB15: J1.171; also elsewhere on the board
/CardEdgeREG/~WBEN: J1.205; also elsewhere on the board
/CardEdgeREG/~WRH: J1.207; also elsewhere on the board
/CardEdgeREG/~WRL: J1.209; also elsewhere on the board
GND: J1.1, J1.4, J1.9, J1.10, J1.11, J1.12, J1.13, J1.14, J1.15, J1.16, J1.17, J1.18, J1.19, J1.20, J1.21, J1.22, J1.23, J1.24, J1.25, J1.26, J1.27, J1.28, J1.29, J1.30, J1.31, J1.32, J1.33, J1.34, J1.35, J1.36, J1.37, J1.38, J1.39, J1.40, J1.41, J1.42, J1.43, J1.44, J1.45, J1.46, J1.47, J1.48, J1.49, J1.50, J1.51, J1.52, J1.53, J1.54, J1.55, J1.56, J1.57, J1.58, J1.59, J1.60, J1.61, J1.62, J1.63, J1.64, J1.65, J1.66, J1.67, J1.68, J1.69, J1.70, J1.71, J1.72, J1.73, J1.74, J1.75, J1.76, J1.77, J1.78, J1.79, J1.80, J1.81, J1.82, J1.83, J1.84, J1.85, J1.86, J1.87, J1.88, J1.89, J1.90, J1.91, J1.92, J1.93, J1.94, J1.95, J1.96, J1.97, J1.98, J1.99, J1.100, J1.101, J1.102, J1.103, J1.104, J1.105, J1.106, J1.107, J1.108, J1.109, J1.110, J1.111, J1.112, J1.113, J1.114, J1.115, J1.116, J1.117, J1.118, J1.119, J1.120, J1.121, J1.122, J1.123, J1.124, J1.125, J1.126, J1.127, J1.128, J1.129, J1.130, J1.131, J1.132, J1.133, J1.134, J1.136, J1.138, J1.140, J1.142, J1.144, J1.146, J1.148, J1.150, J1.152, J1.154, J1.156, J1.158, J1.160, J1.162, J1.164, J1.166, J1.168, J1.170, J1.172, J1.174, J1.176, J1.178, J1.180, J1.182, J1.213, J1.216, J1.218, J1.220, J1.222, J1.224, J1.226, J1.228, J1.230, J1.232, J1.234, J1.236, J1.238, J1.240, J1.242, J1.244, J1.246, J1.248, J1.250, J1.252, J1.254, J1.256, J1.258, J1.260, J1.262, J1.264, J1.266, J1.268, J1.270, J1.272, J1.274, J1.276, J1.278, J1.279; also elsewhere on the board
VCC: J1.2, J1.3, J1.5, J1.6, J1.7, J1.8; also elsewhere on the board

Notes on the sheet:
4-bit card identification code: 0b0110
